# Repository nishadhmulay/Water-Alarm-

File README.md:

<h1 align="center">Water Alarm</h1>

<p align="center">
  A simple water detection alarm that warns you early when moisture or leaks are detected.
</p>

---

## About

Water Alarm is a project designed to detect the presence of water and trigger an alert as soon as moisture is found. It can be used in places like bathrooms, basements, kitchens, near sinks, or around any area where water could potentially cause damage.

---

## Features

- Water detection
- Instant alarm response
- Simple and practical design
- Useful for home safety and monitoring
- Loud buzzer alert
- Compact and easy to install
- Drill mounts
- LED light (Optional)

---

## Renders

<p align="center">

*Pls look at the files for the engineering drawings, BOM, schematics, etc. for more

</p>

---

## Background

This water alarm can be used anywhere, such as near a toilet, sink, or any place where water could potentially flood. It powers a loud buzzer to notify people of a leak and

It was built using components from DigiKey. Schematics, PCB layout, Gerber files, and testing were completed in KiCad, and the engineering drawings were created for the project.

The project helped develop skills in schematic design, PCB design, soldering, and working with electrical components. I truly encourage anyone to try this out, especially if you are new to PCBs and electronics.

---

## Components

# Bill of Materials

| Reference | Part Number/Links | Value | Footprint | Description | Qty | Cost (USD) |
|---|---|---|---|---|---:|---:|
| BZ1 | [668-1652-ND](https://www.digikey.com/en/products/detail/pui-audio-inc/AI-3035-TT-12V-R/9083403?s=N4IgTCBcDaIGxwBwFoCMcCsZkDkAiIAugL5A) | Buzzer | `1_buzzers:Buzzer_D30mm_H20mm_P15mm_668-1652-ND` | Audible alarm | 1 | $6.99 |
| C1 | [56-K102K10X7RH5UL2CT-ND](https://www.digikey.com/en/products/detail/vishay-beyschlag-draloric-bc-components/K102K10X7RH5UL2/2820341?s=N4IgTCBcDaIKwDYC0BpAjABjOjANA7AEoAScAqgDJgDCAKkgHIAiIA) | 0.001 uF | `Capacitor_THT:C_Disc_D3.0mm_W2.0mm_P2.50mm` | Capacitor | 1 | $0.13 |
| D2 (V2) | [1830-1004-ND](https://www.digikey.com/en/products/detail/inolux/INL-3AG30/7604619?s=N4IgTCBcDaIIwA4DMAGAtHFKAsaByAIiALoC%2BQA) | LED | `LED_THT:LED_D3.0mm` | Light emitting diode, small green | 1 | $0.39 |
| J1 | [CP-037A-ND](https://www.digikey.com/en/products/detail/same-sky-formerly-cui-devices/PJ-037A/1644545?s=N4IgTCBcDaIMIAUC0AGAzAdgIJIHIBEQBdAXyA) | Barrel Jack | `Connector_BarrelJack:BarrelJack_Horizontal` | Power input jack | 1 | $1.74 |
| J2 | [2057-EBAA-02-C-ND](https://www.digikey.com/en/products/detail/adam-tech/EBAA-02-C/13586872?s=N4IgTCBcDa4AwFYDsBaAogIQIJZXMKAwigHIAiIAugL5A) | Screw Terminal | `TerminalBlock_Phoenix:TerminalBlock_Phoenix_MKDS-1,5-2_1x02_P5.00mm_Horizontal` | Water sensor connection | 1 | $0.67 |
| Q1 | [4878-2N7000CT-ND](https://www.digikey.com/en/products/detail/diotec-semiconductor/2N7000/13164314?s=N4IgTCBcDaICwA4DsCC0YBySAMuDCAKqhgCIgC6AvkA) | MOSFET | `Package_TO_SOT_THT:TO-92_Inline` | N-channel MOSFET | 1 | $0.47 |
| R1 | [CF18JT10M0CT-ND](https://www.digikey.com/en/products/detail/stackpole-electronics-inc/CF18JT10M0/1741568?s=N4IgTCBcDaIMIDECMAOAUgFSQBgLLbgwFoA5AERAF0BfIA) | Resistor (10M) | `Resistor_THT:R_Axial_DIN0204_L3.6mm_D1.6mm_P5.08mm_Horizontal` | Pull-down resistor | 1 | $0.10 |
| R2 (V2) | [CF18JT330RCT](https://www.digikey.com/en/products/detail/stackpole-electronics-inc/CF18JT330R/1741683) | Resistor (330 Ohms) | `Resistor_THT:R_Axial_DIN0204_L3.6mm_D1.6mm_P5.08mm_Horizontal` | LED current limiting resistor | 1 | $0.10 |
| Z1 | [364-1254-ND](https://www.digikey.com/en/products/detail/tri-mag-llc/L6R06H-120/7682617?s=N4IgTCBcDaIMwDYAsBaAjGArKgcgERAF0BfIA) | 12v Supply | — | Housing | 1 | $6.83 |
| Z2 | [1927-1053-ND](https://www.digikey.com/en/products/detail/kitronik-ltd/4132/8635470?s=N4IgTCBcDaIIwE4wHYC0cAMBWAzKgcgCIgC6AvkA) | Batt Assy | — | Battery Assembly (9v) | 1 | $1.28 |
| - | [Link](https://www.walmart.com/ip/Great-Value-9V-Batteries-2-Pack-Alkaline-9-Volt-Batteries/14359618034?wmlspartner=wlpa&selectedSellerId=0&wl13=688&adid=2222222229714359618034_0000000000_23) |  |  |  |  |  |
| - | [Link](https://www.dxengineering.com/parts/dxe-pw-18?seid=dxese1&gad_source=1&gad_campaignid=18666805149&gclid=CjwKCAjwuczWBhA9EiwAYGgEoXRTcK_Nh8_z7XygRpjv3QG3suuSUEusgzB5P-DtU-ECp1jka1wYjRo) |  |  |  |  |  |
|  |  |  |  |  | *Estimated* | **Subtotal: $19.06** |

Refer to BOM.csv as needed

*The quantity shows a minimum number of components needed to create 1 water alarm. I recommend buying more than 1 component, just to have as back up. Costs may differ if done so

---

## Setup

Components will need to be soldered onto the PCB board carefully, especially the MOSFET (Q1). A wire should be connected to the Terminal Block (J2) with both ends of the wire stripped off to reveal the conductive wire.

## Revisions & Changes

-V1 was the board that was physically built, soldered, and tested. V1 did NOT have a functioning LED light, and only had the buzzer

-V1 Issues: D2 anode had no trace to VCC, and R2's pad went to GND, so LED wouldn't have been activated when the alarm was activated

-V2 Changes: D2 anode to VCC, R2 to the Q1 drain, and R2 changed to CF18JT330R

Note: The LED and R2 are completely optional and haven't been tested. The buzzer works without it. I have included both V1 and V2 schematics and PCB screenshots. 

## CAD File  

https://github.com/nishadhmulay/Water-Alarm-/releases/download/V1/Water.Alarm.CAD.1.step

## Engineer Drawings

- [Water Alarm Engineered Drawings (Exploded)](https://github.com/nishadhmulay/Water-Alarm-/blob/main/Water%20Alarm%20Engineered%20Drawings%20%28Exploded%29%20WA1.0.pdf)
- [Water Alarm Engineered Drawings 2](https://github.com/nishadhmulay/Water-Alarm-/blob/main/Water%20Alarm%20Engineered%20Drawings%202.pdf)
- [Water Alarm Dimensions](https://github.com/nishadhmulay/Water-Alarm-/blob/main/Water%20Alarm%20Dimensions.pdf) 

## Schematic Editor 

- [Schematic Editor](https://github.com/nishadhmulay/Water-Alarm-/blob/main/Schematic%20Editor.png)

---

## Usage

Any 9-volt battery with a barrel plug will work perfectly. The water alarm will continue detecting moisture until the battery lasts (Approx. 1-3 years).

---

## Future Improvements

- 3D printed enclosure
- Adjustable sensitivity
- More wire sensors
- Separated pads for easier soldering

---

## Tips

- Make sure that the solder DOES NOT flow through and connect the pins or pads for the MOSFET (Q1). The solder should cover each independent pad and pin only
- If the buzzer sounds each time the battery is plugged in, check the solder on the back and make sure it's not touching multiple pads/pins. Make sure the wires aren't touching each other
- Don't accidentally place a component the wrong way; always make sure that they follow the outline on the PCB
- Make sure the sensor area stays clean and dry when not in use.
- Test the alarm once in a while to confirm it still works.
- Place the sensor in an area where water would collect first.
- Check all wiring and connections if the alarm is not triggering.
- Replace the battery or power source if the alarm becomes weak.

---

## AI Usage

- Used to figure out how to set the copper area on the PCB
- General definitions and functions of parts, mechanisms, etc.
- Confirming that parts and the entire circuit can work
- Assigning footprints to the LED
- Using and learning GitHub
- Clarifying rules and resources
- Checking for any mistakes in wiring schematics in KiCad
- Learning and tips for soldering

---

## Disclaimer

This project is provided for educational and informational purposes only. Use it at your own risk.

The author is not responsible for any damage, injury, or loss resulting from the use or misuse of this project. This project is not certified for commercial, industrial, or life-safety use.

Always use caution when working with electricity, water, and electronic components.
Good luck!!

---

## License

This project is open source and available under the MIT License.

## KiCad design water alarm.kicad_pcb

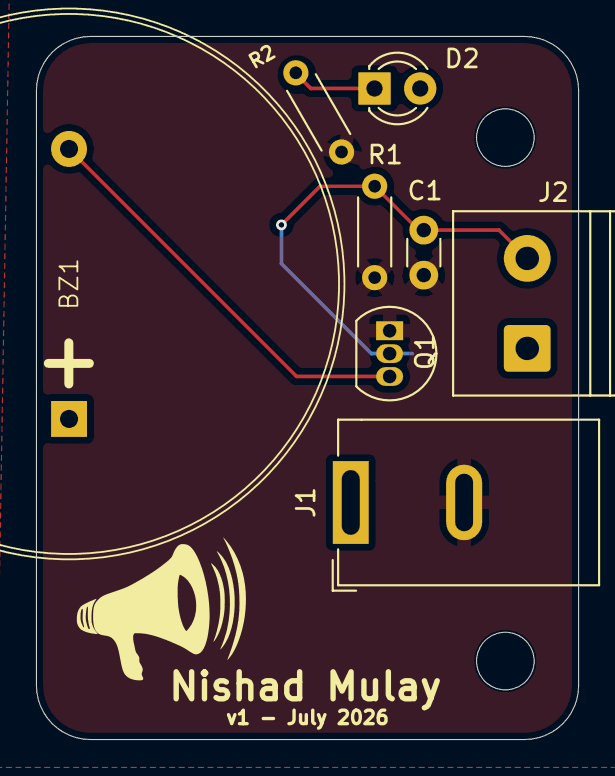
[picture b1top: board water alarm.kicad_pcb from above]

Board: 2 copper layers, 30.1 x 39.1 mm, 8 parts (0 on the bottom side), 5 nets.

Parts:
BZ1: Buzzer; Buzzer_D30mm_H20mm_P15mm_668-1652-ND_AI-3035-TT-12V-R
C1: 1nF; C_Disc_D3.0mm_W1.6mm_P2.50mm
D2: LED_Small_Filled; LED_D3.0mm
J1: Jack-DC; BarrelJack_GCT_DCJ200-10-A_Horizontal
J2: Screw_Terminal_01x02; TerminalBlock_Phoenix_PT-1,5-2-5.0-H_1x02_P5.00mm_Horizontal
Q1: 2N7000; TO-92_Inline
R1: 10M; R_Axial_DIN0204_L3.6mm_D1.6mm_P5.08mm_Horizontal
R2: 330 Ω; R_Axial_DIN0204_L3.6mm_D1.6mm_P5.08mm_Horizontal

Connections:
/Gate: C1.1, J2.2, Q1.2 (G), R1.1
GND: C1.2, J1.2, Q1.1 (S), R1.2, R2.2
unnamed: BZ1.2 (-), Q1.3 (D)
unnamed: D2.1 (K), R2.1
VCC: BZ1.1 (+), J1.1, J2.1
